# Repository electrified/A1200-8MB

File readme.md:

# 8MB Fast Ram for A1200

This is a 8MB FastRam board for A1200 designed in 2019 by @edu_arana, coworked with Stephen Leary based on the TF328 project.

# License

This project, as the same as the original, are released under the GNU GPLv2. If you build a modified version of the board you must supply the end user with all the sources (this can be a web link). Also you may create
or base commercial PCBs from the work in this repository but you must make the sources for all derivative work available. The authors on this board must remain and stay legible on the current / new board. Removing the
copyright notices its a breach of the GPL.

BTW, If you make a new board version, we will be glad if you send at least one pcb to each us. This is not a must :p

# Images

# PCB info (for pcb fabricator)

Dimensions :	59 x 100 mm  
Layers :	4 layers  
Layer order: GTL, G1, G2, GBL  
Finished Copper : 1 oz Cu  
PCB Kinds:	2 (because the breakable area)  
Track/Spacing:	6/6mil  
Blind/Buried Via: No  
Material :	Normal FR-4 Board TG150  
Thickness :	1.6 mm  
Solder Mask :	Whatever color you want :)  
Silkscreen :	Whatever color you want :)  
Surface Finish :Immersion gold (recommended)  
Hole Size :	0.4  

# Firmware:

S. Leary a.k.a terriblefire has made an small modification to the current TF322 to disable the ide option, as the A1200 already have one. The firmware jed files are available on the firmware directory.

Xilinx ISE, 14.7
JTAG Adaptor

Stephen has made a new branch for the firmware used on this board. The current branch address is https://github.com/terriblefire/tf328/tree/edu1200_board

Thanks S.

# Gerbers:

Premade gerbers of the board are available on this repository too.

# Bill of matherials

Note that the only ram chips used and compatible are the K4E151612C, this ram chips are 3v3 only. All the current design is adapter to 3V3. A new LDO regulator is used to get 3V3 vots.

| Part          | Value                   | Package                        |
| ------------- | ----------------------- | ------------------------------ |   
| C1            | 1uF                     | 1206                           |
| C2            | 10uF                    | 1206                           | 
| C3            | 10uF                    | 1206                           | 
| C5            | 1uF                     | 1206                           |
| CN1           | A1200-EXPANSION_SLOT    | CON_150                        | 
| IC1           | K4E151612C              | TSOP44(50)-II                  | 
| IC2           | K4E151612C              | TSOP44(50)-II                  | 
| IC3           | K4E151612C              | TSOP44(50)-II                  | 
| IC4           | K4E151612C              | TSOP44(50)-II                  | 
| IC6           | LD39150DT33-R           | STD5N52U                       | 
| ICC1          | 10uF                    | 1206                           | 
| ICC2          | 10uF                    | 1206                           | 
| ICC3          | 10uF                    | 1206                           | 
| ICC4          | 10uF                    | 1206                           | 
| MUXCPLD       | XC9536_44VQ             | SQFP-S-10X10-44                | 
| RAMCPLD       | XC9572XL-VQ64           | VQ64                           |

# Wiki

There is a TF328 wiki that can be use to resolve any doubt about the compatibility of the current firmware.

https://github.com/terriblefire/tf328/wiki

# PCMCIA Fix

If you got problems with your PCMCIA device and this upgrade, you can use a free software solution available on aminet called CardReset http://aminet.net/package/util/boot/CardReset

# Contribution / support

If you wanna buy me a beer or a Mercedes SLR,  please contact me at info at arananet.net or support @terriblefire at youtube :)

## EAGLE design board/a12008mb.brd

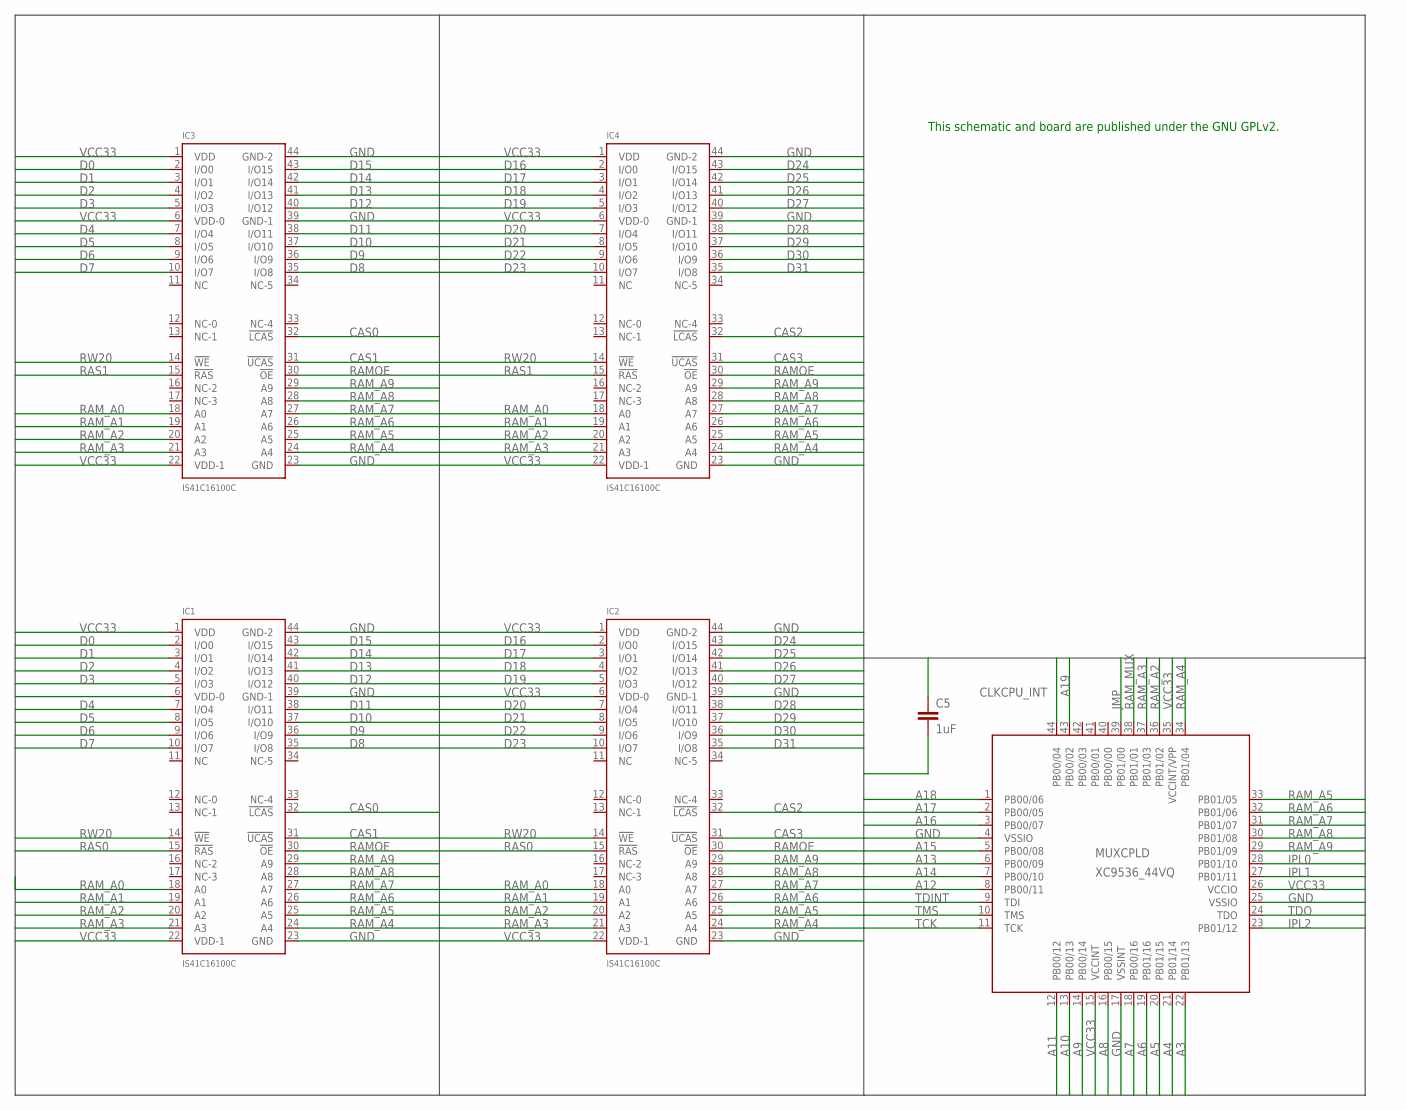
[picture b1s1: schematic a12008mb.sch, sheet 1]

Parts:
C5: 1uF; C1206
IC1, IC2, IC3, IC4: IS41C16100C; TSOP44(50)-II
MUXCPLD: XC9536_44VQ; SQFP-S-10X10-44

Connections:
A3: MUXCPLD.22 (PB01/13); also elsewhere on the board
A4: MUXCPLD.21 (PB01/14); also elsewhere on the board
A5: MUXCPLD.20 (PB01/15); also elsewhere on the board
A6: MUXCPLD.19 (PB01/16); also elsewhere on the board
A7: MUXCPLD.18 (PB00/16); also elsewhere on the board
A8: MUXCPLD.16 (PB00/15); also elsewhere on the board
A9: MUXCPLD.14 (PB00/14); also elsewhere on the board
A10: MUXCPLD.13 (PB00/13); also elsewhere on the board
A11: MUXCPLD.12 (PB00/12); also elsewhere on the board
A12: MUXCPLD.8 (PB00/11); also elsewhere on the board
A13: MUXCPLD.6 (PB00/09); also elsewhere on the board
A14: MUXCPLD.7 (PB00/10); also elsewhere on the board
A15: MUXCPLD.5 (PB00/08); also elsewhere on the board
A16: MUXCPLD.3 (PB00/07); also elsewhere on the board
A17: MUXCPLD.2 (PB00/05); also elsewhere on the board
A18: MUXCPLD.1 (PB00/06); also elsewhere on the board
A19: MUXCPLD.43 (PB00/02); also elsewhere on the board
CAS0: IC1.32 (!LCAS), IC3.32 (!LCAS); also elsewhere on the board
CAS1: IC1.31 (!UCAS), IC3.31 (!UCAS); also elsewhere on the board
CAS2: IC2.32 (!LCAS), IC4.32 (!LCAS); also elsewhere on the board
CAS3: IC2.31 (!UCAS), IC4.31 (!UCAS); also elsewhere on the board
CLKCPU_INT: MUXCPLD.44 (PB00/04)
D0: IC1.2 (I/O0), IC3.2 (I/O0); also elsewhere on the board
D1: IC1.3 (I/O1), IC3.3 (I/O1); also elsewhere on the board
D2: IC1.4 (I/O2), IC3.4 (I/O2); also elsewhere on the board
D3: IC1.5 (I/O3), IC3.5 (I/O3); also elsewhere on the board
D4: IC1.7 (I/O4), IC3.7 (I/O4); also elsewhere on the board
D5: IC1.8 (I/O5), IC3.8 (I/O5); also elsewhere on the board
D6: IC1.9 (I/O6), IC3.9 (I/O6); also elsewhere on the board
D7: IC1.10 (I/O7), IC3.10 (I/O7); also elsewhere on the board
D8: IC1.35 (I/O8), IC3.35 (I/O8); also elsewhere on the board
D9: IC1.36 (I/O9), IC3.36 (I/O9); also elsewhere on the board
D10: IC1.37 (I/O10), IC3.37 (I/O10); also elsewhere on the board
D11: IC1.38 (I/O11), IC3.38 (I/O11); also elsewhere on the board
D12: IC1.40 (I/O12), IC3.40 (I/O12); also elsewhere on the board
D13: IC1.41 (I/O13), IC3.41 (I/O13); also elsewhere on the board
D14: IC1.42 (I/O14), IC3.42 (I/O14); also elsewhere on the board
D15: IC1.43 (I/O15), IC3.43 (I/O15); also elsewhere on the board
D16: IC2.2 (I/O0), IC4.2 (I/O0); also elsewhere on the board
D17: IC2.3 (I/O1), IC4.3 (I/O1); also elsewhere on the board
D18: IC2.4 (I/O2), IC4.4 (I/O2); also elsewhere on the board
D19: IC2.5 (I/O3), IC4.5 (I/O3); also elsewhere on the board
D20: IC2.7 (I/O4), IC4.7 (I/O4); also elsewhere on the board
D21: IC2.8 (I/O5), IC4.8 (I/O5); also elsewhere on the board
D22: IC2.9 (I/O6), IC4.9 (I/O6); also elsewhere on the board
D23: IC2.10 (I/O7), IC4.10 (I/O7); also elsewhere on the board
D24: IC2.43 (I/O15), IC4.43 (I/O15); also elsewhere on the board
D25: IC2.42 (I/O14), IC4.42 (I/O14); also elsewhere on the board
D26: IC2.41 (I/O13), IC4.41 (I/O13); also elsewhere on the board
D27: IC2.40 (I/O12), IC4.40 (I/O12); also elsewhere on the board
D28: IC2.38 (I/O11), IC4.38 (I/O11); also elsewhere on the board
D29: IC2.37 (I/O10), IC4.37 (I/O10); also elsewhere on the board
D30: IC2.36 (I/O9), IC4.36 (I/O9); also elsewhere on the board
D31: IC2.35 (I/O8), IC4.35 (I/O8); also elsewhere on the board
GND: C5.2, IC1.23 (GND), IC1.39 (GND-1), IC1.44 (GND-2), IC2.23 (GND), IC2.39 (GND-1), IC2.44 (GND-2), IC3.23 (GND), IC3.39 (GND-1), IC3.44 (GND-2), IC4.23 (GND), IC4.39 (GND-1), IC4.44 (GND-2), MUXCPLD.4 (VSSIO), MUXCPLD.17 (VSSINT), MUXCPLD.25 (VSSIO); also elsewhere on the board
IPL0: MUXCPLD.28 (PB01/10); also elsewhere on the board
IPL1: MUXCPLD.27 (PB01/11); also elsewhere on the board
IPL2: MUXCPLD.23 (PB01/12); also elsewhere on the board
JMP: MUXCPLD.39 (PB01/00)
RAMOE: IC1.30 (!OE), IC2.30 (!OE), IC3.30 (!OE), IC4.30 (!OE); also elsewhere on the board
RAM_A0: IC1.18 (A0), IC2.18 (A0), IC3.18 (A0), IC4.18 (A0); also elsewhere on the board
RAM_A1: IC1.19 (A1), IC2.19 (A1), IC3.19 (A1), IC4.19 (A1); also elsewhere on the board
RAM_A2: IC1.20 (A2), IC2.20 (A2), IC3.20 (A2), IC4.20 (A2), MUXCPLD.36 (PB01/02)
RAM_A3: IC1.21 (A3), IC2.21 (A3), IC3.21 (A3), IC4.21 (A3), MUXCPLD.37 (PB01/03)
RAM_A4: IC1.24 (A4), IC2.24 (A4), IC3.24 (A4), IC4.24 (A4), MUXCPLD.34 (PB01/04)
RAM_A5: IC1.25 (A5), IC2.25 (A5), IC3.25 (A5), IC4.25 (A5), MUXCPLD.33 (PB01/05)
RAM_A6: IC1.26 (A6), IC2.26 (A6), IC3.26 (A6), IC4.26 (A6), MUXCPLD.32 (PB01/06)
RAM_A7: IC1.27 (A7), IC2.27 (A7), IC3.27 (A7), IC4.27 (A7), MUXCPLD.31 (PB01/07)
RAM_A8: IC1.28 (A8), IC2.28 (A8), IC3.28 (A8), IC4.28 (A8), MUXCPLD.30 (PB01/08)
RAM_A9: IC1.29 (A9), IC2.29 (A9), IC3.29 (A9), IC4.29 (A9), MUXCPLD.29 (PB01/09)
RAM_MUX: MUXCPLD.38 (PB01/01); also elsewhere on the board
RAS0: IC1.15 (!RAS), IC2.15 (!RAS); also elsewhere on the board
RAS1: IC3.15 (!RAS), IC4.15 (!RAS); also elsewhere on the board
RW20: IC1.14 (!WE), IC2.14 (!WE), IC3.14 (!WE), IC4.14 (!WE); also elsewhere on the board
TCK: MUXCPLD.11 (TCK); also elsewhere on the board
TDINT: MUXCPLD.9 (TDI); also elsewhere on the board
TDO: MUXCPLD.24 (TDO); also elsewhere on the board
TMS: MUXCPLD.10 (TMS); also elsewhere on the board
VCC33: C5.1, IC1.1 (VDD), IC1.6 (VDD-0), IC1.22 (VDD-1), IC2.1 (VDD), IC2.6 (VDD-0), IC2.22 (VDD-1), IC3.1 (VDD), IC3.6 (VDD-0), IC3.22 (VDD-1), IC4.1 (VDD), IC4.6 (VDD-0), IC4.22 (VDD-1), MUXCPLD.15 (VCCINT), MUXCPLD.26 (VCCIO), MUXCPLD.35 (VCCINT/VPP); also elsewhere on the board

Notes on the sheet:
This schematic and board are published under the GNU GPLv2.

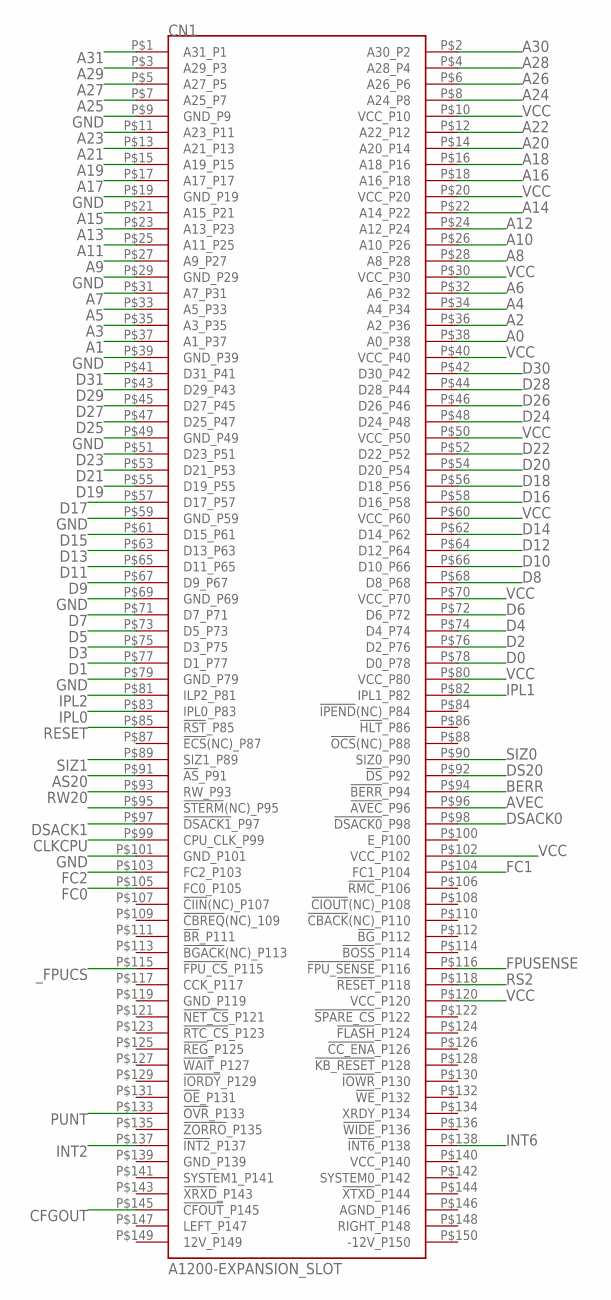
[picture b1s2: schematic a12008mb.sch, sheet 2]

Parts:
CN1: A1200-EXPANSION_SLOT; CON_150

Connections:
A0: CN1.P$38 (A0_P38); also elsewhere on the board
A1: CN1.P$37 (A1_P37); also elsewhere on the board
A2: CN1.P$36 (A2_P36); also elsewhere on the board
A3: CN1.P$35 (A3_P35); also elsewhere on the board
A4: CN1.P$34 (A4_P34); also elsewhere on the board
A5: CN1.P$33 (A5_P33); also elsewhere on the board
A6: CN1.P$32 (A6_P32); also elsewhere on the board
A7: CN1.P$31 (A7_P31); also elsewhere on the board
A8: CN1.P$28 (A8_P28); also elsewhere on the board
A9: CN1.P$27 (A9_P27); also elsewhere on the board
A10: CN1.P$26 (A10_P26); also elsewhere on the board
A11: CN1.P$25 (A11_P25); also elsewhere on the board
A12: CN1.P$24 (A12_P24); also elsewhere on the board
A13: CN1.P$23 (A13_P23); also elsewhere on the board
A14: CN1.P$22 (A14_P22); also elsewhere on the board
A15: CN1.P$21 (A15_P21); also elsewhere on the board
A16: CN1.P$18 (A16_P18); also elsewhere on the board
A17: CN1.P$17 (A17_P17); also elsewhere on the board
A18: CN1.P$16 (A18_P16); also elsewhere on the board
A19: CN1.P$15 (A19_P15); also elsewhere on the board
A20: CN1.P$14 (A20_P14); also elsewhere on the board
A21: CN1.P$13 (A21_P13); also elsewhere on the board
A22: CN1.P$12 (A22_P12); also elsewhere on the board
A23: CN1.P$11 (A23_P11); also elsewhere on the board
A24: CN1.P$8 (A24_P8)
A25: CN1.P$7 (A25_P7)
A26: CN1.P$6 (A26_P6)
A27: CN1.P$5 (A27_P5)
A28: CN1.P$4 (A28_P4)
A29: CN1.P$3 (A29_P3)
A30: CN1.P$2 (A30_P2)
A31: CN1.P$1 (A31_P1)
AS20: CN1.P$91 (!AS!_P91); also elsewhere on the board
AVEC: CN1.P$96 (!AVEC!_P96)
BERR: CN1.P$94 (!BERR!_P94)
CFGOUT: CN1.P$145 (!CFOUT!_P145)
CLKCPU: CN1.P$99 (CPU_CLK_P99); also elsewhere on the board
D0: CN1.P$78 (D0_P78); also elsewhere on the board
D1: CN1.P$77 (D1_P77); also elsewhere on the board
D2: CN1.P$76 (D2_P76); also elsewhere on the board
D3: CN1.P$75 (D3_P75); also elsewhere on the board
D4: CN1.P$74 (D4_P74); also elsewhere on the board
D5: CN1.P$73 (D5_P73); also elsewhere on the board
D6: CN1.P$72 (D6_P72); also elsewhere on the board
D7: CN1.P$71 (D7_P71); also elsewhere on the board
D8: CN1.P$68 (D8_P68); also elsewhere on the board
D9: CN1.P$67 (D9_P67); also elsewhere on the board
D10: CN1.P$66 (D10_P66); also elsewhere on the board
D11: CN1.P$65 (D11_P65); also elsewhere on the board
D12: CN1.P$64 (D12_P64); also elsewhere on the board
D13: CN1.P$63 (D13_P63); also elsewhere on the board
D14: CN1.P$62 (D14_P62); also elsewhere on the board
D15: CN1.P$61 (D15_P61); also elsewhere on the board
D16: CN1.P$58 (D16_P58); also elsewhere on the board
D17: CN1.P$57 (D17_P57); also elsewhere on the board
D18: CN1.P$56 (D18_P56); also elsewhere on the board
D19: CN1.P$55 (D19_P55); also elsewhere on the board
D20: CN1.P$54 (D20_P54); also elsewhere on the board
D21: CN1.P$53 (D21_P53); also elsewhere on the board
D22: CN1.P$52 (D22_P52); also elsewhere on the board
D23: CN1.P$51 (D23_P51); also elsewhere on the board
D24: CN1.P$48 (D24_P48); also elsewhere on the board
D25: CN1.P$47 (D25_P47); also elsewhere on the board
D26: CN1.P$46 (D26_P46); also elsewhere on the board
D27: CN1.P$45 (D27_P45); also elsewhere on the board
D28: CN1.P$44 (D28_P44); also elsewhere on the board
D29: CN1.P$43 (D29_P43); also elsewhere on the board
D30: CN1.P$42 (D30_P42); also elsewhere on the board
D31: CN1.P$41 (D31_P41); also elsewhere on the board
DS20: CN1.P$92 (!DS!_P92); also elsewhere on the board
DSACK0: CN1.P$98 (!DSACK0!_P98); also elsewhere on the board
DSACK1: CN1.P$97 (!DSACK1!_P97); also elsewhere on the board
FC0: CN1.P$105 (FC0_P105)
FC1: CN1.P$104 (FC1_P104)
FC2: CN1.P$103 (FC2_P103)
FPUSENSE: CN1.P$116 (!FPU_SENSE!_P116)
GND: CN1.P$9 (GND_P9), CN1.P$19 (GND_P19), CN1.P$29 (GND_P29), CN1.P$39 (GND_P39), CN1.P$49 (GND_P49), CN1.P$59 (GND_P59), CN1.P$69 (GND_P69), CN1.P$79 (GND_P79), CN1.P$101 (GND_P101); also elsewhere on the board
INT2: CN1.P$137 (!INT2!_P137); also elsewhere on the board
INT6: CN1.P$138 (!INT6!_P138)
IPL0: CN1.P$83 (IPL0_P83); also elsewhere on the board
IPL1: CN1.P$82 (IPL1_P82); also elsewhere on the board
IPL2: CN1.P$81 (ILP2_P81); also elsewhere on the board
PUNT: CN1.P$133 (!OVR!_P133); also elsewhere on the board
RESET: CN1.P$85 (!RST!_P85); also elsewhere on the board
RS2: CN1.P$118 (!RESET!_P118)
RW20: CN1.P$93 (RW_P93); also elsewhere on the board
SIZ0: CN1.P$90 (SIZ0_P90); also elsewhere on the board
SIZ1: CN1.P$89 (SIZ1_P89); also elsewhere on the board
VCC: CN1.P$10 (VCC_P10), CN1.P$20 (VCC_P20), CN1.P$30 (VCC_P30), CN1.P$40 (VCC_P40), CN1.P$50 (VCC_P50), CN1.P$60 (VCC_P60), CN1.P$70 (VCC_P70), CN1.P$80 (VCC_P80), CN1.P$102 (VCC_P102), CN1.P$120 (VCC_P120); also elsewhere on the board
_FPUCS: CN1.P$115 (!FPU_CS!_P115)

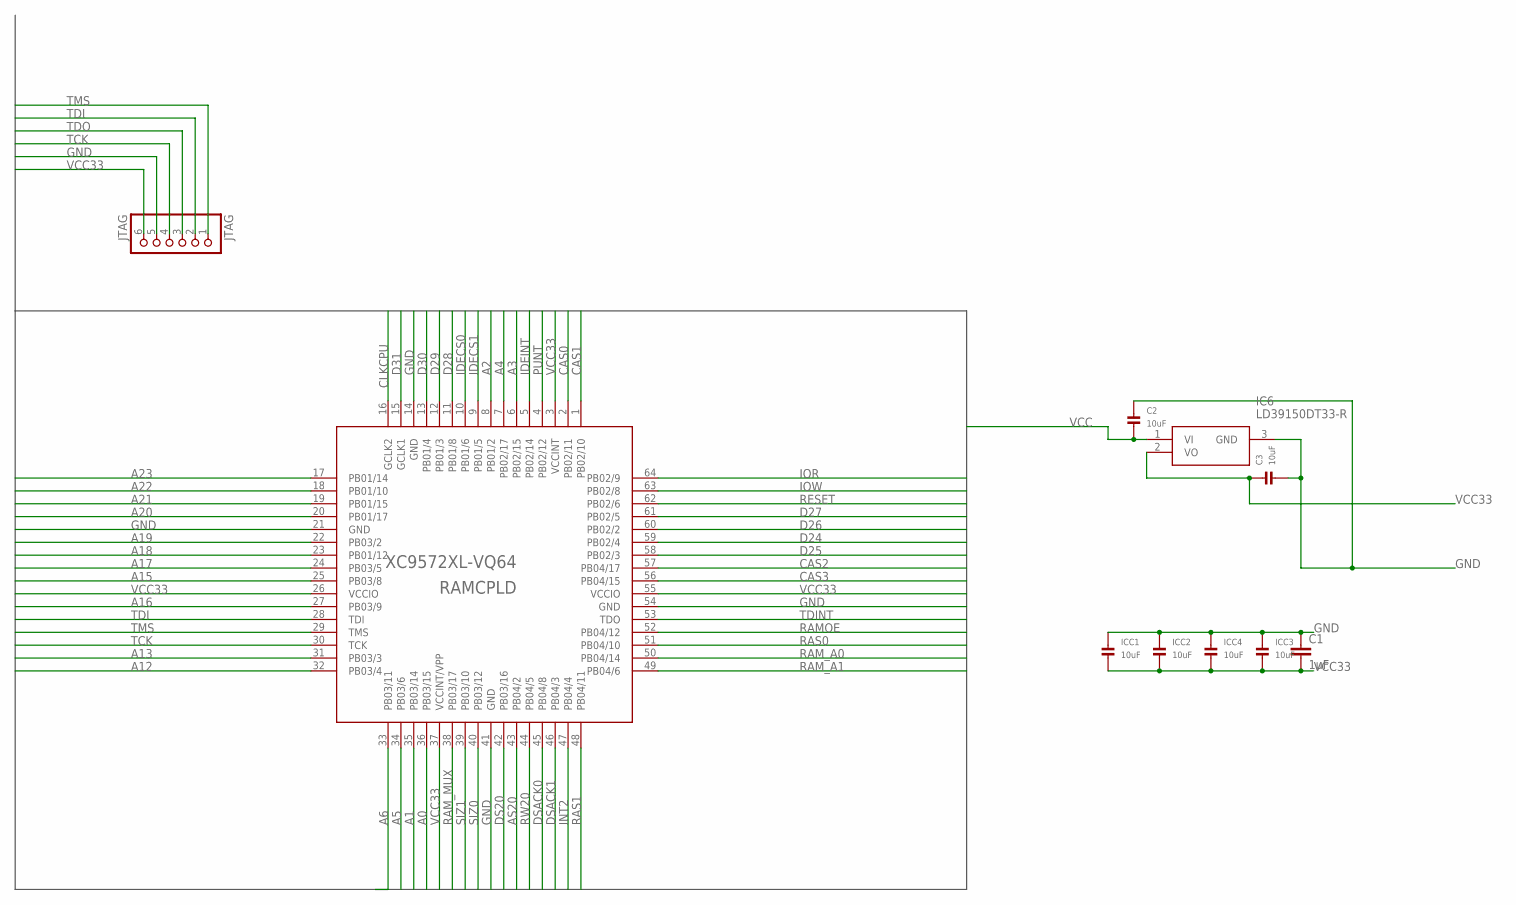
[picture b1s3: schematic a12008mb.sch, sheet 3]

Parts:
C1: 1uF; C1206
C2, C3: 10uF; 1206
IC6: LD39150DT33-R; STD5N52U
ICC1, ICC2, ICC3, ICC4: 10uF; 1206
JTAG: JTAG; 1X06_ROUND
RAMCPLD: XC9572XL-VQ64; VQ64

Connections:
A0: RAMCPLD.36 (PB03/15); also elsewhere on the board
A1: RAMCPLD.35 (PB03/14); also elsewhere on the board
A2: RAMCPLD.8 (PB01/2); also elsewhere on the board
A3: RAMCPLD.6 (PB02/15); also elsewhere on the board
A4: RAMCPLD.7 (PB02/17); also elsewhere on the board
A5: RAMCPLD.34 (PB03/6); also elsewhere on the board
A6: RAMCPLD.33 (PB03/11); also elsewhere on the board
A12: RAMCPLD.32 (PB03/4); also elsewhere on the board
A13: RAMCPLD.31 (PB03/3); also elsewhere on the board
A15: RAMCPLD.25 (PB03/8); also elsewhere on the board
A16: RAMCPLD.27 (PB03/9); also elsewhere on the board
A17: RAMCPLD.24 (PB03/5); also elsewhere on the board
A18: RAMCPLD.23 (PB01/12); also elsewhere on the board
A19: RAMCPLD.22 (PB03/2); also elsewhere on the board
A20: RAMCPLD.20 (PB01/17); also elsewhere on the board
A21: RAMCPLD.19 (PB01/15); also elsewhere on the board
A22: RAMCPLD.18 (PB01/10); also elsewhere on the board
A23: RAMCPLD.17 (PB01/14); also elsewhere on the board
AS20: RAMCPLD.43 (PB04/2); also elsewhere on the board
CAS0: RAMCPLD.2 (PB02/11); also elsewhere on the board
CAS1: RAMCPLD.1 (PB02/10); also elsewhere on the board
CAS2: RAMCPLD.57 (PB04/17); also elsewhere on the board
CAS3: RAMCPLD.56 (PB04/15); also elsewhere on the board
CLKCPU: RAMCPLD.16 (GCLK2); also elsewhere on the board
D24: RAMCPLD.59 (PB02/4); also elsewhere on the board
D25: RAMCPLD.58 (PB02/3); also elsewhere on the board
D26: RAMCPLD.60 (PB02/2); also elsewhere on the board
D27: RAMCPLD.61 (PB02/5); also elsewhere on the board
D28: RAMCPLD.11 (PB01/8); also elsewhere on the board
D29: RAMCPLD.12 (PB01/3); also elsewhere on the board
D30: RAMCPLD.13 (PB01/4); also elsewhere on the board
D31: RAMCPLD.15 (GCLK1); also elsewhere on the board
DS20: RAMCPLD.42 (PB03/16); also elsewhere on the board
DSACK0: RAMCPLD.45 (PB04/8); also elsewhere on the board
DSACK1: RAMCPLD.46 (PB04/3); also elsewhere on the board
GND: C1.1, C2.1, C3.2, IC6.3 (GND), ICC1.1, ICC2.1, ICC3.1, ICC4.1, JTAG.5, RAMCPLD.14 (GND), RAMCPLD.21 (GND), RAMCPLD.41 (GND), RAMCPLD.54 (GND); also elsewhere on the board
IDECS0: RAMCPLD.10 (PB01/6)
IDECS1: RAMCPLD.9 (PB01/5)
IDEINT: RAMCPLD.5 (PB02/14)
INT2: RAMCPLD.47 (PB04/4); also elsewhere on the board
IOR: RAMCPLD.64 (PB02/9)
IOW: RAMCPLD.63 (PB02/8)
PUNT: RAMCPLD.4 (PB02/12); also elsewhere on the board
RAMOE: RAMCPLD.52 (PB04/12); also elsewhere on the board
RAM_A0: RAMCPLD.50 (PB04/14); also elsewhere on the board
RAM_A1: RAMCPLD.49 (PB04/6); also elsewhere on the board
RAM_MUX: RAMCPLD.38 (PB03/17); also elsewhere on the board
RAS0: RAMCPLD.51 (PB04/10); also elsewhere on the board
RAS1: RAMCPLD.48 (PB04/11); also elsewhere on the board
RESET: RAMCPLD.62 (PB02/6); also elsewhere on the board
RW20: RAMCPLD.44 (PB04/5); also elsewhere on the board
SIZ0: RAMCPLD.40 (PB03/12); also elsewhere on the board
SIZ1: RAMCPLD.39 (PB03/10); also elsewhere on the board
TCK: JTAG.4, RAMCPLD.30 (TCK); also elsewhere on the board
TDI: JTAG.2, RAMCPLD.28 (TDI)
TDINT: RAMCPLD.53 (TDO); also elsewhere on the board
TDO: JTAG.3; also elsewhere on the board
TMS: JTAG.1, RAMCPLD.29 (TMS); also elsewhere on the board
VCC: C2.2, IC6.1 (VI); also elsewhere on the board
VCC33: C1.2, C3.1, IC6.2 (VO), ICC1.2, ICC2.2, ICC3.2, ICC4.2, JTAG.6, RAMCPLD.3 (VCCINT), RAMCPLD.26 (VCCIO), RAMCPLD.37 (VCCINT/VPP), RAMCPLD.55 (VCCIO); also elsewhere on the board

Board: 4 copper layers, 17 parts (7 on the bottom side), 96 nets, no tracks yet.

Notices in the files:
board/a12008mb.brd:
GNU Public License (GPL) v2
parts and their libraries:
microbuilder: This work is placed in the public domain, and may be freely used for commercial and non-commercial work with the following conditions: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
